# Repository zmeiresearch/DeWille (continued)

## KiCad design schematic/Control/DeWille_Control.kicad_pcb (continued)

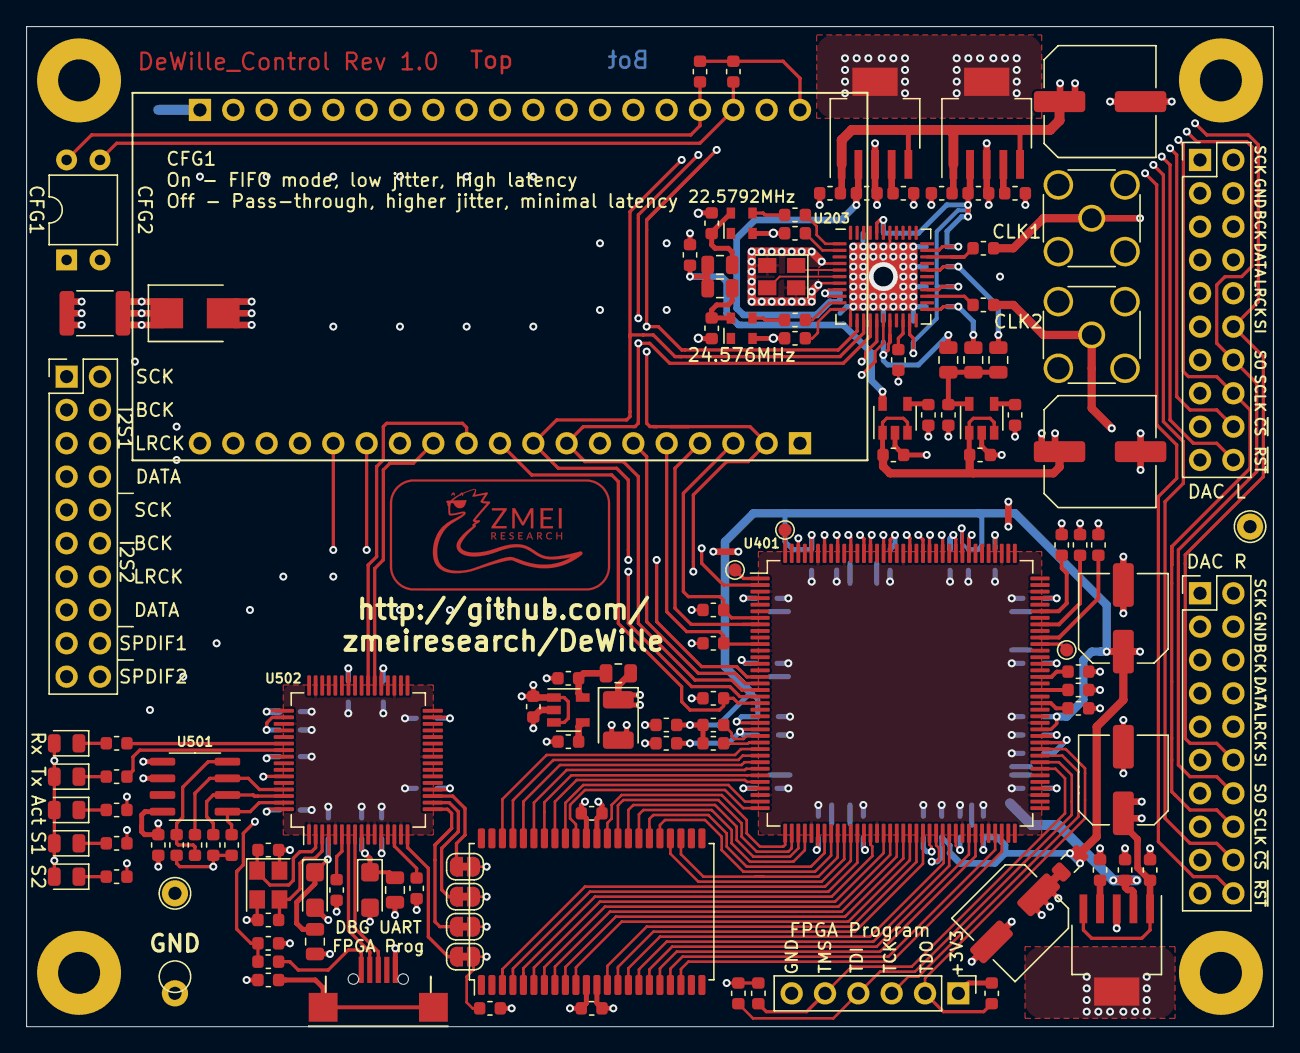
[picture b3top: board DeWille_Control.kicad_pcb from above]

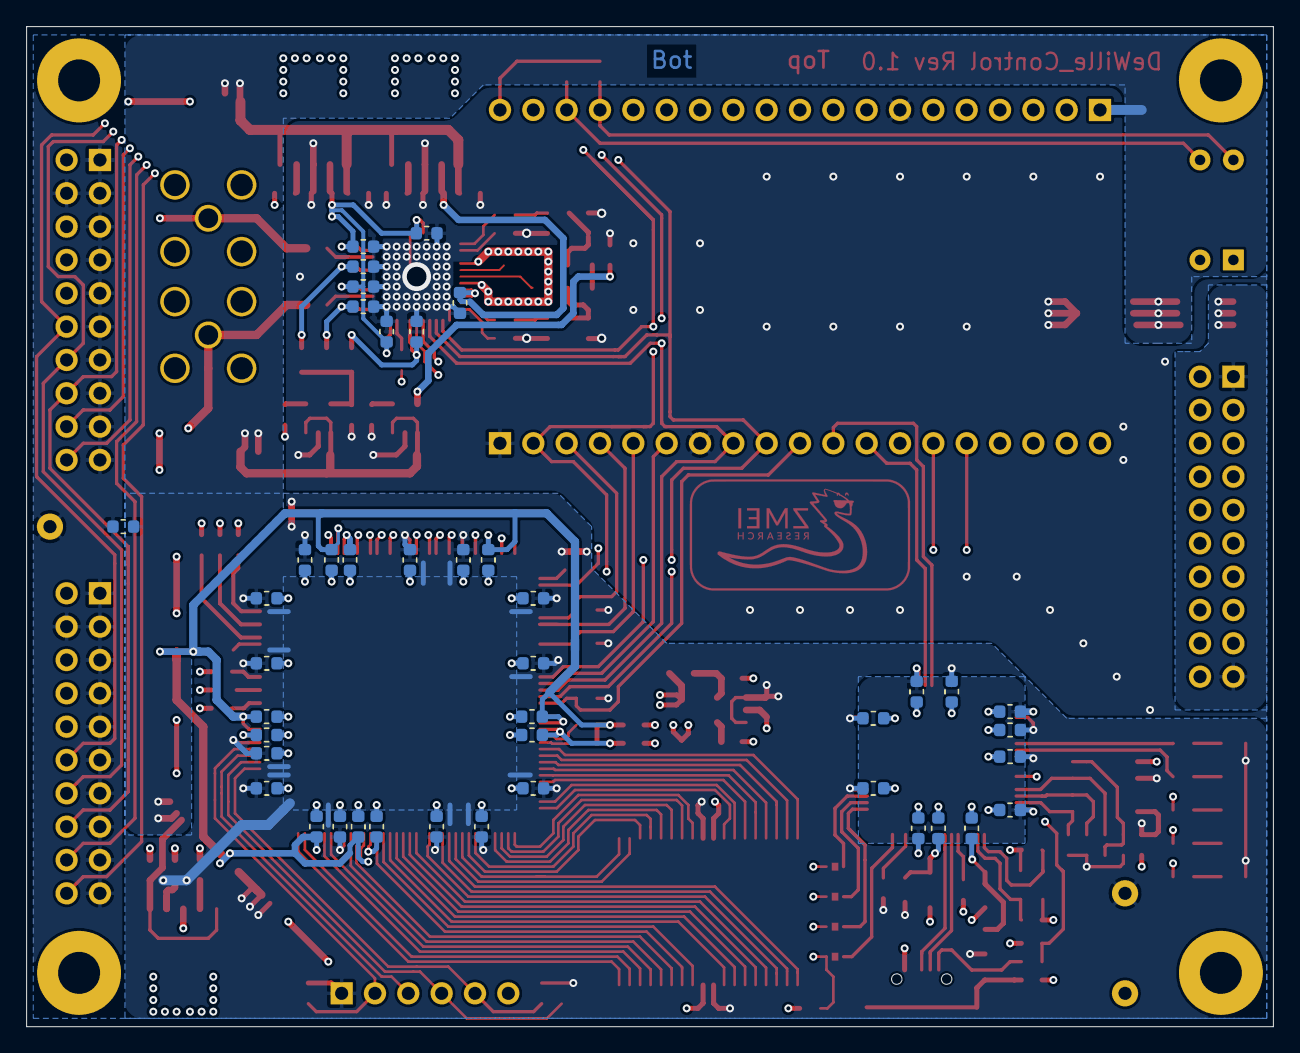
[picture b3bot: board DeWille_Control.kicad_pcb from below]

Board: 4 copper layers, 95.0 x 76.2 mm, 171 parts (43 on the bottom side), 149 nets.

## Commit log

2019-11-12 Clock generation mostly complete. Some inter-module connections fixed.
2019-11-13 Add some info on FPGA choice
2019-11-16 Remove galvanic isolator - too much jitter! Add USB interface for Debug and program purposes. Swith to Lattice FPGA
2019-11-16 Ignore .DS_Store files
2019-11-16 Split design on Base, Control and DAC boards
2019-11-17 Control board diagram complete at high level - Clock, USB, Control, Power and IO done. Remaining is FPGA pin assignment which will be done later to optimize board layout.
2019-11-19 Provision for SPI Slave FPGA bitstream download. Switch RAM from x16 to x8 one.
2019-11-22 Interim commit
2019-11-22 Ignore some utility files
2019-11-23 Routing complete
2019-11-23 Add Licensing information
2019-11-24 Add source termination resistors to I2S output lines. Arrange top silk information.
2019-11-24 Arrange bottom silk screen. Remove obsolete files.
2019-11-24 Add some testpads. Fix +3V3_FPGA track mix-up after termination addition.
2019-11-24 Add decoupling cap between +5V and GND
2019-11-26 Swap BCK and LRCK outputs. Misc small touch-ups on the board
2019-11-26 Add PCM1794 DAC board.
2019-11-27 Send for manufacturing Control and DAC1794 boards.
2019-12-03 Add Base board schematic
2019-12-09 Base schematic complete
2019-12-29 Check-in of misc. sch changes to Base
2020-01-02 Update Readme and add construction log.
2020-01-08 Add Changes.txt, listing future changes to the schematic and boards Finish up Base board routing
2020-01-20 Add some additional notes for future revisions
2020-01-20 Add Base_v1.0 fabrication files
2020-01-20 Update construction log
2020-02-06 Updated Changes.md after Base Board test construction
2020-02-06 Add small comment for GND poly on DAC board
2020-02-06 Add Media files
2020-02-06 Make naming consistent
2020-02-06 Add information on Base Board regulator test. Trying to include some pictures as well.
2020-02-06 Add more photos
2020-02-06 Fixed location of in-progress photo
2020-03-15 Add PlatformIO project for ESP32
2020-03-16 Add mention of ESP32 powering
2020-03-16 Small refactoring.
2020-03-17 Fix indent and braces
2020-03-17 Fix BlinkTask stack size so that the system actually starts.
2020-03-22 Add logging implementation
2020-03-24 Add notes about UART0 pin usage and Rx/Tx LEDs
2020-03-24 Ignore vim .swp files
2020-03-24 Switch logging to FT2232 UART and make it work
2020-03-26 Managed to read ID from Si5344.
2020-03-28 Add Out-of-memory status value
2020-03-28 Make private data static
2020-03-28 Implement correct register reading & debug output
2020-03-28 Add some comments on Si534x driver
2020-03-28 Rename Si5344->Si534x to indicate that it's a generic driver. Move register definitions to si5344_regs.h as not to clutter the main code
2020-03-28 Implement page setting and ready polling
2020-03-28 Add all Si534x registers
2020-03-28 Allow banks A and B as well
2020-03-28 Implement device ID reading
2020-03-29 Move Software/ESP32/DeWille_PIO -> Software/Control/ESP32_PlatformIO Add ClockBuilder project and output for Si5344.
2020-03-29 Rename Si534x files
2020-03-29 Add a script to merge multiple Si534x configurations in a single file
2020-03-30 Add some remarks on the Clock circuit
2020-03-30 Implement Si534x config information retrieval.
2020-03-31 Implement Si534x config setting from ClockBuilderPro register export
2020-04-04 Implement configuration writing for Si5344
2020-04-04 Finish SiMerge script so that it can generate the whole config file now.
2020-04-04 Increase logging buffer
2020-04-04 Fix some issues in writeBuffer
2020-04-04 Rename spi.[h/cpp] => spi_mux.[h/cpp], otherwise spi.h<=>SPI.h causes issues on case non-sensitive systems.
2020-04-04 Add Si5344 status register dump
2020-04-05 Bump SPI speed to 500kHz
2020-04-05 Fix an error that prevented properly setting configuration - it always wrote to page 0. Allowed page 8 to be accessed as well - ClockBuilderPro generates values for it. Add more debug output
2020-04-20 My first Verilog module. Yay!
2020-04-20 Reimplement the testbench to use an external test vector file. Add a simple Makefile to help with instrumentation
2020-04-20 Ignore lxt2 files from Verilog simulation
2020-04-20 Use macros for test vector input file. Use extended arguments for testbench waveform output file.
    Move all simulation output in a subfolder.
2020-04-20 Ignore all sim/ folders
2020-04-27 Add notes about the JFET CCS
2020-05-04 Add mention to allow easier plug-in of various inputs
2020-05-04 Add skeleton dualport_ram module
2020-07-12 Add simple verilog dual-port ram
2020-07-12 Remove dualport_ram - not needed
2020-07-29 Initial support for PCM1792
2020-07-29 Fix typo
2020-08-02 Add config.h to repo
2020-08-02 Initial version of DeWille web interface - firmware and SPIFFS upload
2020-08-05 Style a little the web interface page with Milligram
2020-08-09 Move ARRAY_SIZE to globals.h -> used in at least three places already.
2020-08-09 Initial support for websocket logging
2020-08-10 Remote client able to connect to websocket logger
2020-08-12 Reorganize component interaction, introduce pseudo-modules.
2020-08-12 Add port.h - platform-specific stuff that is used by multiple components
2020-08-13 Make Websocket logging work
2020-08-14 Update DAC communication code - read/write check succeeds.
2020-08-16 Make output work. Sound played from I2S source.
2020-08-16 Add FPGA passthrough sample project.
